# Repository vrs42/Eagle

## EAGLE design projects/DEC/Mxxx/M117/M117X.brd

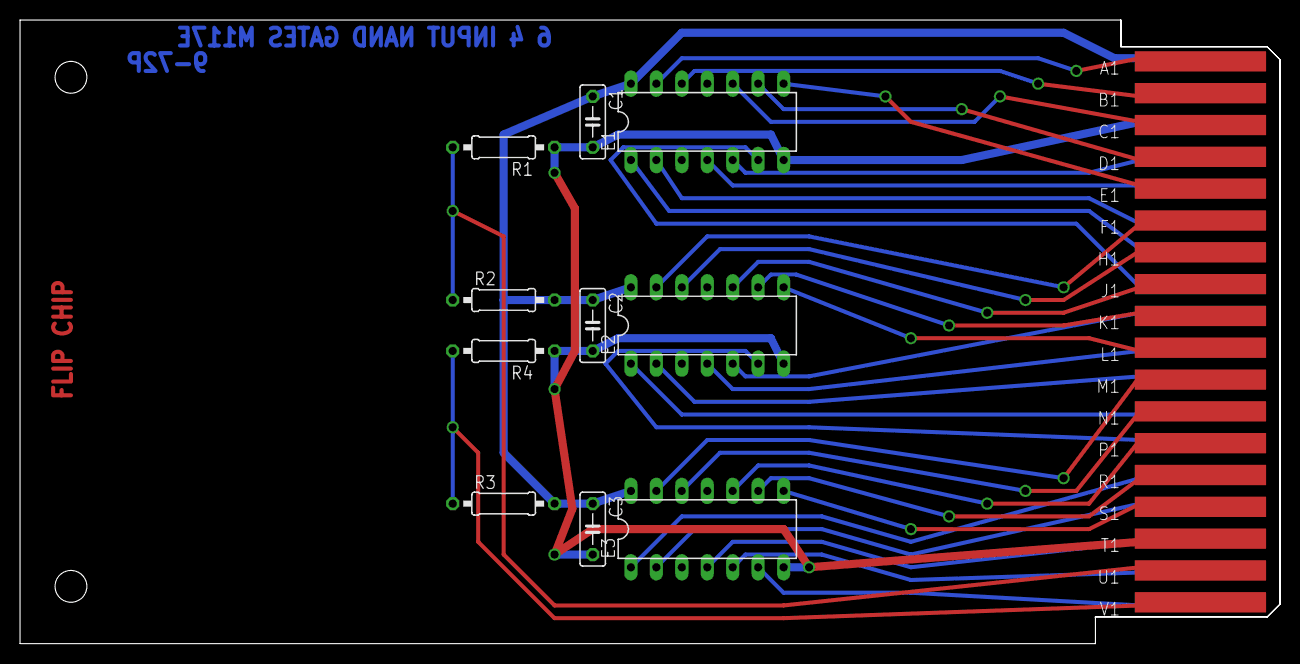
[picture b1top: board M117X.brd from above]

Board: 2 copper layers, 125.7 x 62.2 mm, 12 parts (0 on the bottom side), 34 nets.

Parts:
C1, C2, C3: .01uf; C050-025X075
E1, E2, E3: 7420N; DIL14
R1, R4: 750 5%; 0207/10
R2, R3: 330 10%; 0207/10
U$1: EDGE-CON2
U$4: OUTLINE-SINGLE; SINGLE

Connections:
A1: E1.13, U$1.A1
B1: E1.12, U$1.B1
C1: E1.10, U$1.C1
D1: E1.9, U$1.D1
D2: E1.5, U$1.D2
E1: E1.8, U$1.E1
E2: E1.4, U$1.E2
F1: E2.13, U$1.F1
F2: E1.2, U$1.F2
GND: C1.2, C2.2, C3.2, E1.7, E2.7, E3.7, R1.1, R4.1, U$1.C2, U$1.T1
H1: E2.12, U$1.H1
H2: E1.1, U$1.H2
J1: E2.10, U$1.J1
J2: E1.6, U$1.J2
K1: E2.9, U$1.K1
K2: E2.5, U$1.K2
L1: E2.8, U$1.L1
L2: E2.4, U$1.L2
M1: E3.13, U$1.M1
M2: E2.2, U$1.M2
N1: E3.12, U$1.N1
N2: E2.1, U$1.N2
P1: E3.10, U$1.P1
P2: E2.6, U$1.P2
R1: E3.9, U$1.R1
R2: E3.1, U$1.R2
S1: E3.8, U$1.S1
S2: E3.2, U$1.S2
T2: E3.4, U$1.T2
U1: R1.2, R2.1, U$1.U1
U2: E3.5, U$1.U2
V1: R3.1, R4.2, U$1.V1
V2: E3.6, U$1.V2
VCC: C1.1, C2.1, C3.1, E1.14, E2.14, E3.14, R2.2, R3.2, U$1.A2

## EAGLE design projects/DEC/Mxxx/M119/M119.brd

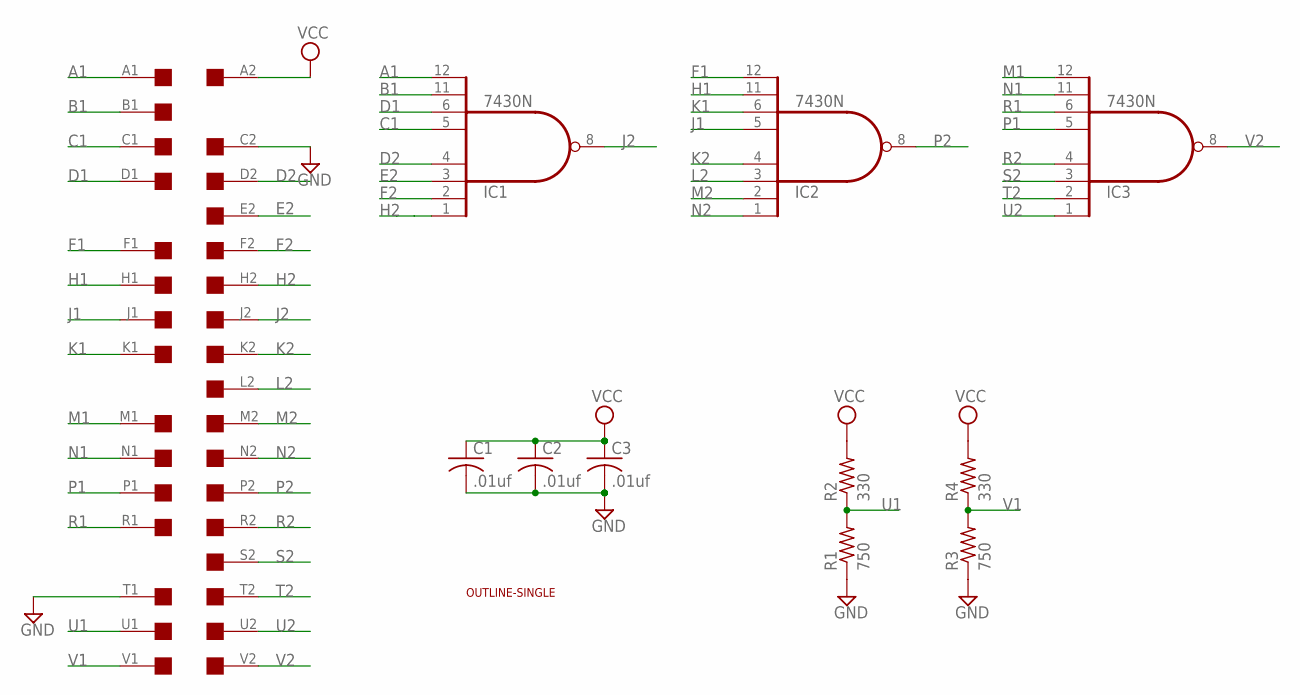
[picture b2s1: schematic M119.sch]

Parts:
C1, C2, C3: .01uf; C050-025X075
IC1, IC2, IC3: 7430N; DIL14
R1, R3: 750; 0207/10
R2, R4: 330; 0207/10
U$1: OUTLINE-SINGLE; SINGLE
U$4: SINGLE; EDGE-CON2

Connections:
A1: IC1.12 (I7), U$4.A1
B1: IC1.11 (I6), U$4.B1
C1: IC1.5 (I4), U$4.C1
D1: IC1.6 (I5), U$4.D1
D2: IC1.4 (I3), U$4.D2
E2: IC1.3 (I2), U$4.E2
F1: IC2.12 (I7), U$4.F1
F2: IC1.2 (I1), U$4.F2
GND: C1.2, C2.2, C3.2, IC1.7 (GND), IC2.7 (GND), IC3.7 (GND), R1.1, R3.1, U$4.C2, U$4.T1
H1: IC2.11 (I6), U$4.H1
H2: IC1.1 (I0), U$4.H2
J1: IC2.5 (I4), U$4.J1
J2: IC1.8 (O), U$4.J2
K1: IC2.6 (I5), U$4.K1
K2: IC2.4 (I3), U$4.K2
L2: IC2.3 (I2), U$4.L2
M1: IC3.12 (I7), U$4.M1
M2: IC2.2 (I1), U$4.M2
N1: IC3.11 (I6), U$4.N1
N2: IC2.1 (I0), U$4.N2
P1: IC3.5 (I4), U$4.P1
P2: IC2.8 (O), U$4.P2
R1: IC3.6 (I5), U$4.R1
R2: IC3.4 (I3), U$4.R2
S2: IC3.3 (I2), U$4.S2
T2: IC3.2 (I1), U$4.T2
U1: R1.2, R2.1, U$4.U1
U2: IC3.1 (I0), U$4.U2
V1: R3.2, R4.1, U$4.V1
V2: IC3.8 (O), U$4.V2
VCC: C1.1, C2.1, C3.1, IC1.14 (VCC), IC2.14 (VCC), IC3.14 (VCC), R2.2, R4.2, U$4.A2

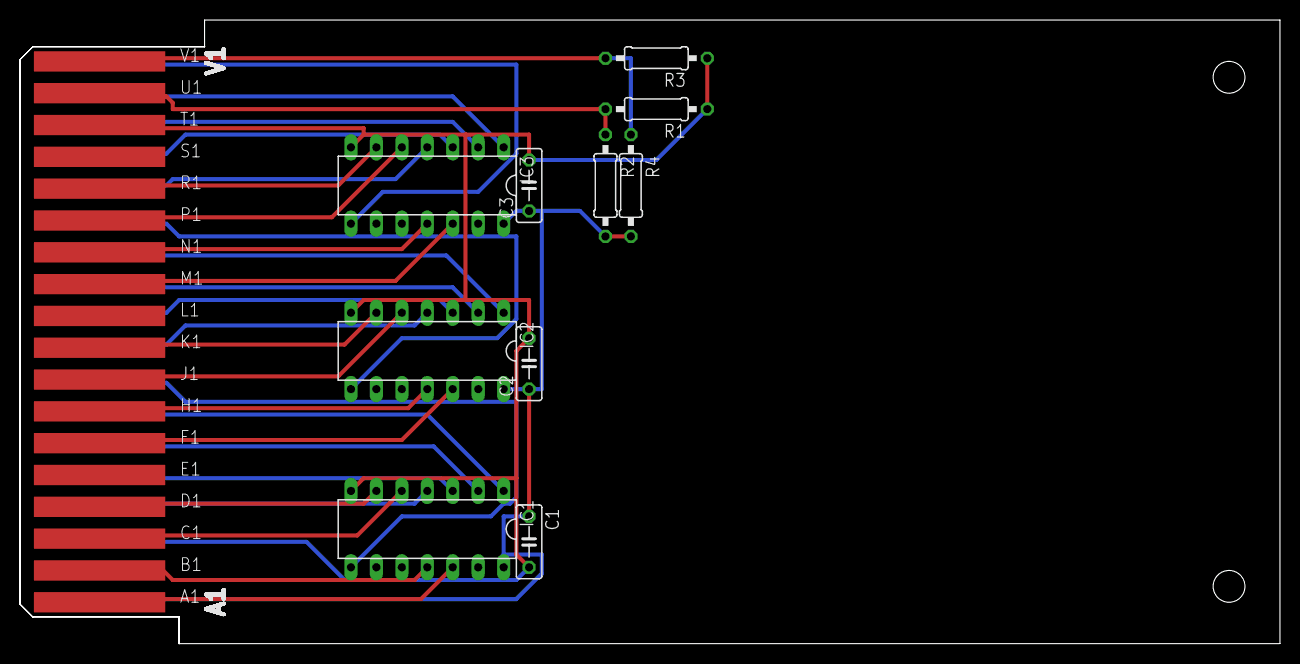
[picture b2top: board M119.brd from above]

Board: 2 copper layers, 125.7 x 62.2 mm, 12 parts (0 on the bottom side), 31 nets.

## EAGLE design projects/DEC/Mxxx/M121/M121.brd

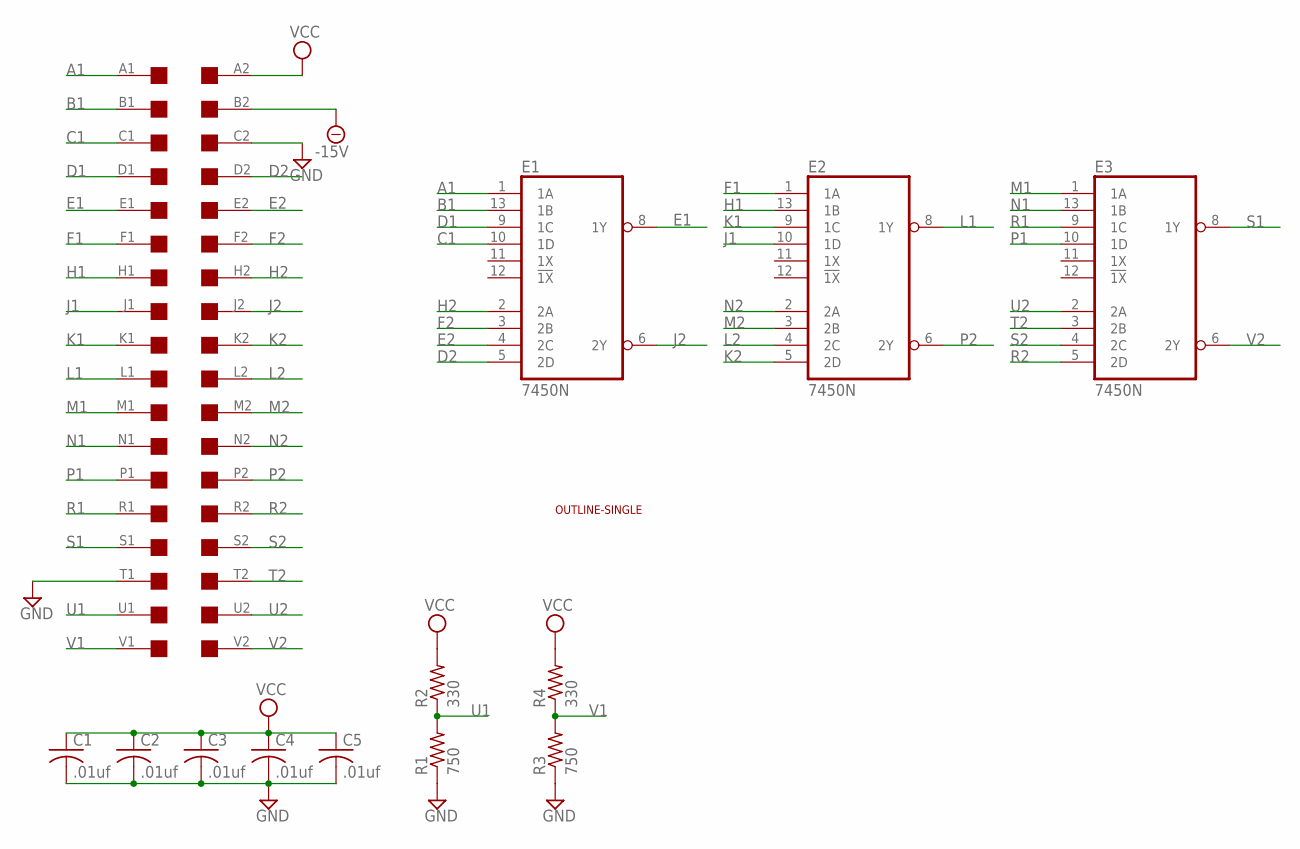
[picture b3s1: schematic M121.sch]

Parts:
C1, C2, C3, C4, C5: .01uf; C050-025X075
E1, E2, E3: 7450N; DIL14
R1, R3: 750; 0207/10
R2, R4: 330; 0207/10
U$1: OUTLINE-SINGLE; SINGLE
U$4: SINGLE; EDGE-CON2

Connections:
-15V: U$4.B2
A1: E1.1 (1A), U$4.A1
B1: E1.13 (1B), U$4.B1
C1: E1.10 (1D), U$4.C1
D1: E1.9 (1C), U$4.D1
D2: E1.5 (2D), U$4.D2
E1: E1.8 (1Y), U$4.E1
E2: E1.4 (2C), U$4.E2
F1: E2.1 (1A), U$4.F1
F2: E1.3 (2B), U$4.F2
GND: C1.2, C2.2, C3.2, C4.2, C5.2, E1.7 (GND), E2.7 (GND), E3.7 (GND), R1.1, R3.1, U$4.C2, U$4.T1
H1: E2.13 (1B), U$4.H1
H2: E1.2 (2A), U$4.H2
J1: E2.10 (1D), U$4.J1
J2: E1.6 (2Y), U$4.J2
K1: E2.9 (1C), U$4.K1
K2: E2.5 (2D), U$4.K2
L1: E2.8 (1Y), U$4.L1
L2: E2.4 (2C), U$4.L2
M1: E3.1 (1A), U$4.M1
M2: E2.3 (2B), U$4.M2
N1: E3.13 (1B), U$4.N1
N2: E2.2 (2A), U$4.N2
P1: E3.10 (1D), U$4.P1
P2: E2.6 (2Y), U$4.P2
R1: E3.9 (1C), U$4.R1
R2: E3.5 (2D), U$4.R2
S1: E3.8 (1Y), U$4.S1
S2: E3.4 (2C), U$4.S2
T2: E3.3 (2B), U$4.T2
U1: R1.2, R2.1, U$4.U1
U2: E3.2 (2A), U$4.U2
V1: R3.2, R4.1, U$4.V1
V2: E3.6 (2Y), U$4.V2
VCC: C1.1, C2.1, C3.1, C4.1, C5.1, E1.14 (VCC), E2.14 (VCC), E3.14 (VCC), R2.2, R4.2, U$4.A2

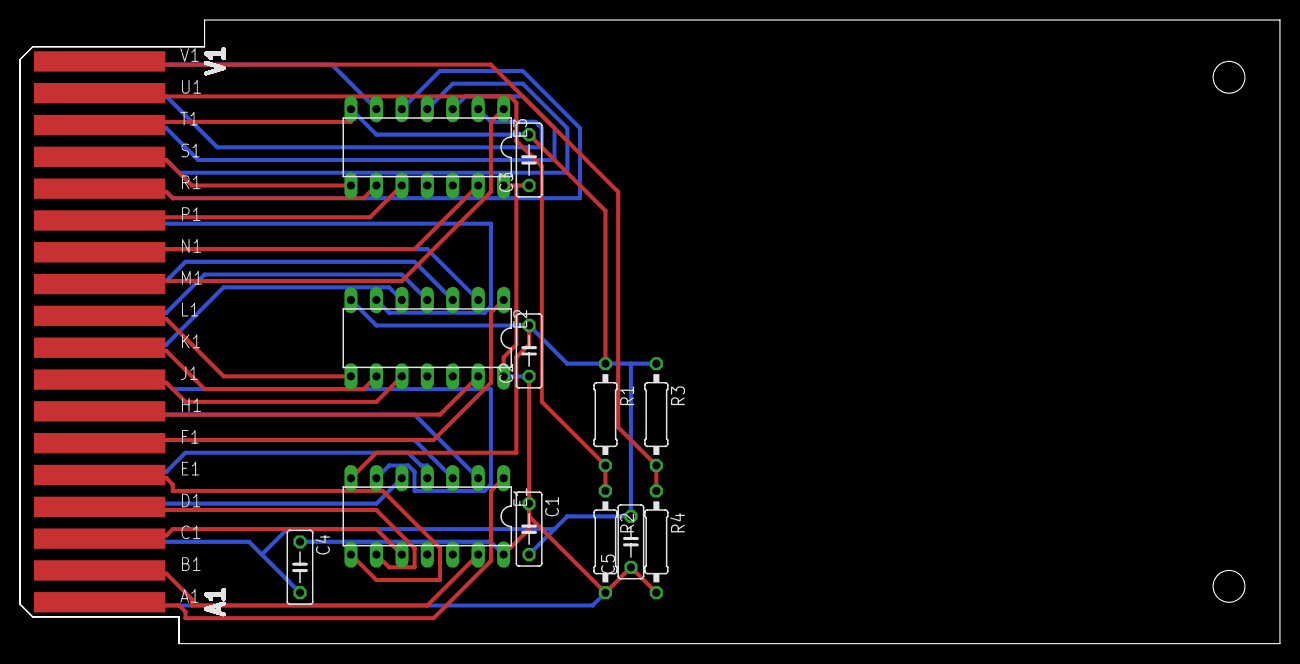
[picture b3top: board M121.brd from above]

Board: 2 copper layers, 125.7 x 62.2 mm, 14 parts (0 on the bottom side), 34 nets.
